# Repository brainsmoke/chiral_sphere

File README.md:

# Chiral Sphere

LED lamp based on a chiral spherical tiling consisting of 20 triangles and
12 Pentagons where the edge-length ratio triangle:pentagon is 2:1.

[Video](https://mastodon.social/@brainsmoke/111589632039788005)

# Materials

* 2x 5m WS2812 LED strips, 60 LEDs/m spacing, 10mm wide, cut into 30 strips of 17
* +/- 11 meters flexible diffuser, 12mm wide
* [custom joint PCBs [kicad]](pcb/yjoint) [[svg]](pcb/yjoint/penta_joint.svg), [untested flexpcb alternative [kicad]](pcb/yjoint_v2) [[svg]](pcb/yjoint_v2/penta_joint_v2.svg)
* [LED driver board](https://github.com/brainsmoke/leddriver3d/tree/main/pcb/driver_slim_v1), [LED driver board v2](https://github.com/brainsmoke/leddriver3d/tree/main/pcb/driver_slim_v2)
* thin wire (for connecting the data lines)
* 2x ~30cm thick wire (to handle high currents near the power connector)
* 3mm plywood, 4x 600x400mm
* white paint
* wood glue

# Maths

* [Formula for the relation between corner arc and edge-length for regular N-gons on the unit sphere](https://github.com/brainsmoke/geometry/blob/main/spherical/ngonmath.png)
* [Calculation of the corner arc for this spherical tiling](https://github.com/brainsmoke/geometry/blob/main/spherical/2tri1penta.scad#L8-L34)
* [LED Locations & normals](https://github.com/brainsmoke/geometry/blob/main/scripts/led_locations.py)

# Cutting

Based on output from [one of my scripts](https://github.com/brainsmoke/geometry/blob/main/scripts/tube.py), but
with the outer panels removed so that the tubes become U-profiles and the sides modified so that they trace
a perfect sphere.

[Laser cut shapes](cut/v1/led.svg) (with some spares; apply appropriate kerf width compensation before cutting)

# Wiring

All strips are positioned such that data-in is above data-out, with one pentagon chosen
as top.  The strips are connected as five point-symmetrical led strips with 102 LEDs each
according to [this OpenSCAD model](doc/wiring.scad).

# LED Driver

[PCB](https://github.com/brainsmoke/leddriver3d/tree/main/pcb/driver_slim_v1)

# Software

* [Driver software repo](https://github.com/brainsmoke/leddriver3d)
* [STM32 Firmware: strip5.bin](https://github.com/brainsmoke/leddriver3d/tree/main/firmware/stm32/strip5)
* [LED positions](https://github.com/brainsmoke/leddriver3d/blob/main/firmware/esp32/models/chiral_tiling/leds.json)
* [conf/hardware.json](https://github.com/brainsmoke/leddriver3d/blob/main/firmware/esp32/conf/chiral_tiling/hardware.json)

# More pictures

Add extra capacity to the strip which needs to handle the most Amps.

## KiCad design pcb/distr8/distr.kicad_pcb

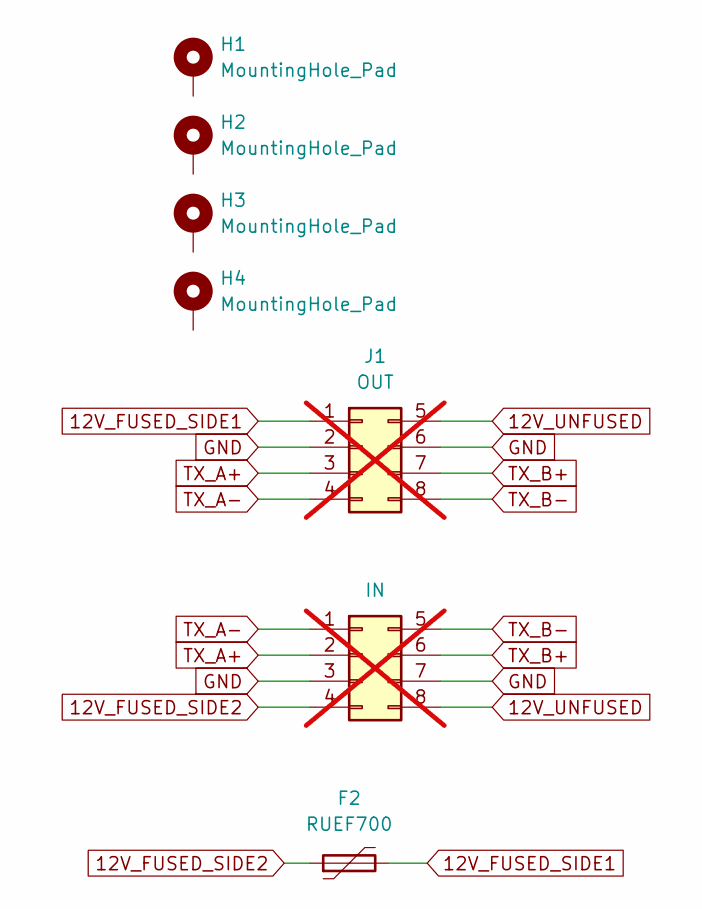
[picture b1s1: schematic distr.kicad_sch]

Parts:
F2: RUEF700; Fuse_Littlefuse_RUEF
H1, H2, H3, H4: MountingHole_Pad
J1: OUT; Molex_Micro-Fit_3.0_43045-0800_2x04_P3.00mm_Horizontal; not fitted
J2: IN; Molex_Micro-Fit_3.0_43045-0800_2x04_P3.00mm_Horizontal; not fitted

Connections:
12V_FUSED_SIDE1: F2.2, J1.1
12V_FUSED_SIDE2: F2.1, J2.4
12V_UNFUSED: J1.5, J2.8
GND: J1.2, J1.6, J2.3, J2.7
TX_A+: J1.3, J2.2
TX_A-: J1.4, J2.1
TX_B+: J1.7, J2.6
TX_B-: J1.8, J2.5

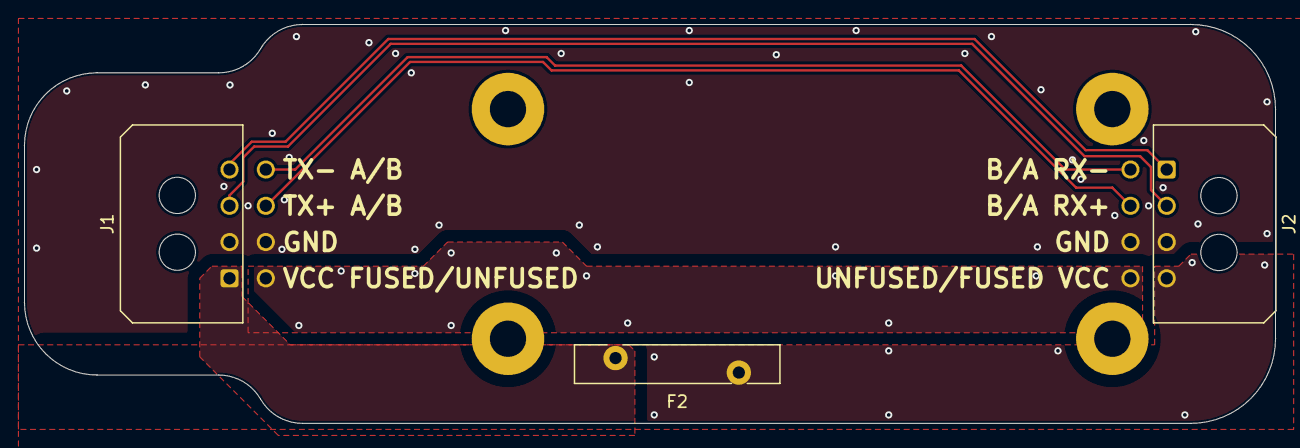
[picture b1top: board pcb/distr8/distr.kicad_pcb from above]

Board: 2 copper layers, 103.5 x 33.0 mm, 7 parts (0 on the bottom side), 8 nets.

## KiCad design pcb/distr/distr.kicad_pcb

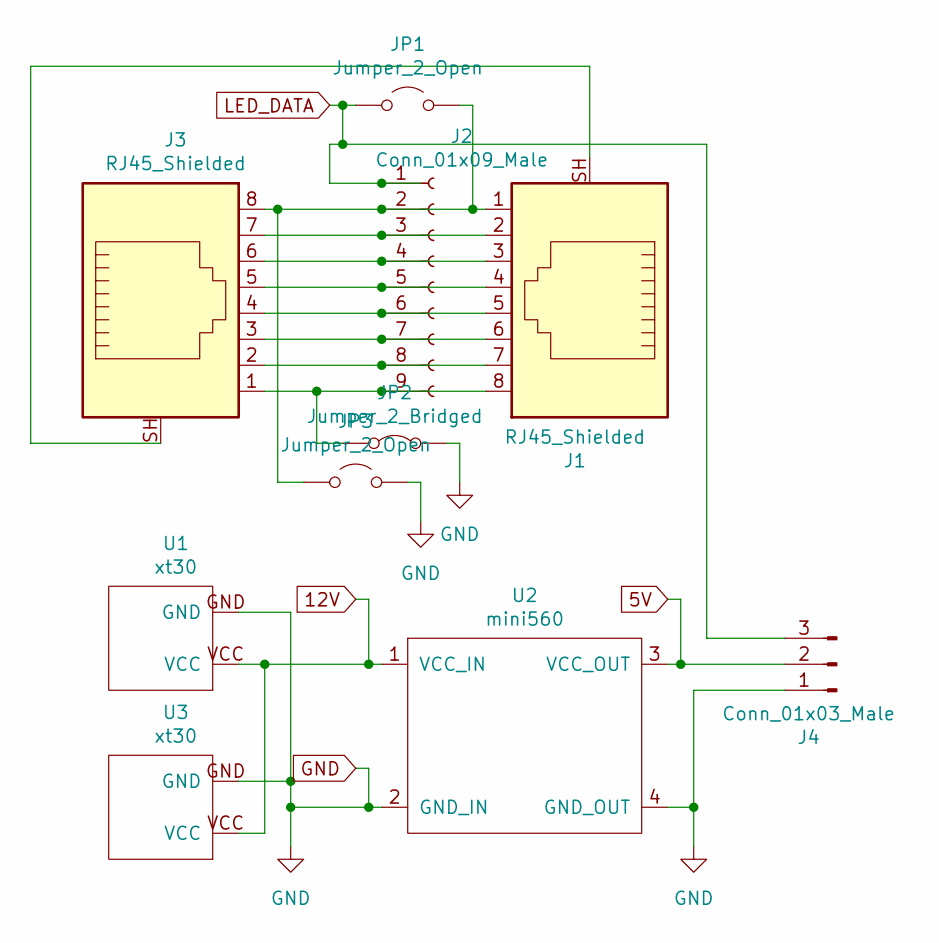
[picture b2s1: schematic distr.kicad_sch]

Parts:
J1, J3: RJ45_Shielded; HC-RJ45-055-7
J2: Conn_01x09_Male; PinHeader_1x09_P2.54mm_Vertical
J4: Conn_01x03_Male; PinHeader_1x03_P2.54mm_Vertical
JP1: Jumper_2_Open; SolderJumper-2_P1.3mm_Open_TrianglePad1.0x1.5mm
JP2: Jumper_2_Bridged; SolderJumper-2_P1.3mm_Bridged_RoundedPad1.0x1.5mm
JP3: Jumper_2_Open; SolderJumper-2_P1.3mm_Open_RoundedPad1.0x1.5mm
U1: xt30; xt30-PW-F_banana
U2: mini560
U3: xt30; xt30-PW-M_banana

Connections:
5V: J4.2, U2.3 (VCC_OUT)
12V: U1.VCC, U2.1 (VCC_IN), U3.VCC
GND: J4.1, JP2.2 (B), JP3.2 (B), U1.GND, U2.2 (GND_IN), U2.4 (GND_OUT), U3.GND
LED_DATA: J2.1, J4.3, JP1.1 (A)
unnamed: J1.SH, J3.SH
unnamed: J1.1, J2.2, J3.8, JP1.2 (B), JP3.1 (A)
unnamed: J1.2, J2.3, J3.7
unnamed: J1.3, J2.4, J3.6
unnamed: J1.4, J2.5, J3.5
unnamed: J1.5, J2.6, J3.4
unnamed: J1.6, J2.7, J3.3
unnamed: J1.7, J2.8, J3.2
unnamed: J1.8, J2.9, J3.1, JP2.1 (A)

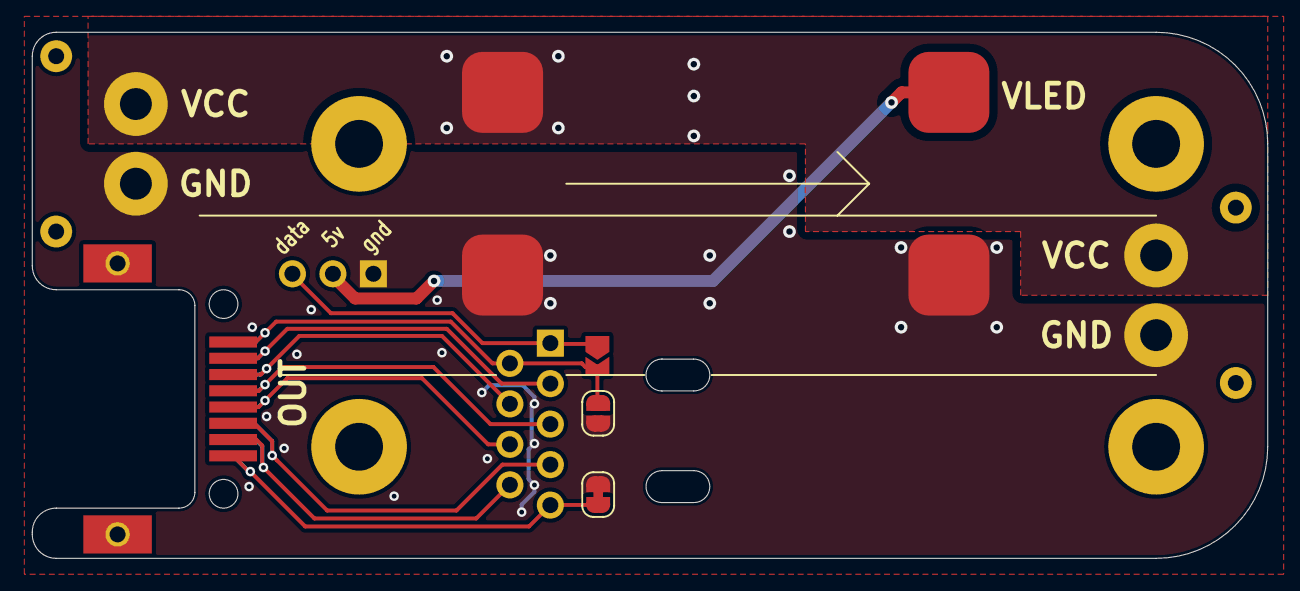
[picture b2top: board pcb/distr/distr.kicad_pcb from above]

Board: 2 copper layers, 77.5 x 33.0 mm, 10 parts (1 on the bottom side), 13 nets.

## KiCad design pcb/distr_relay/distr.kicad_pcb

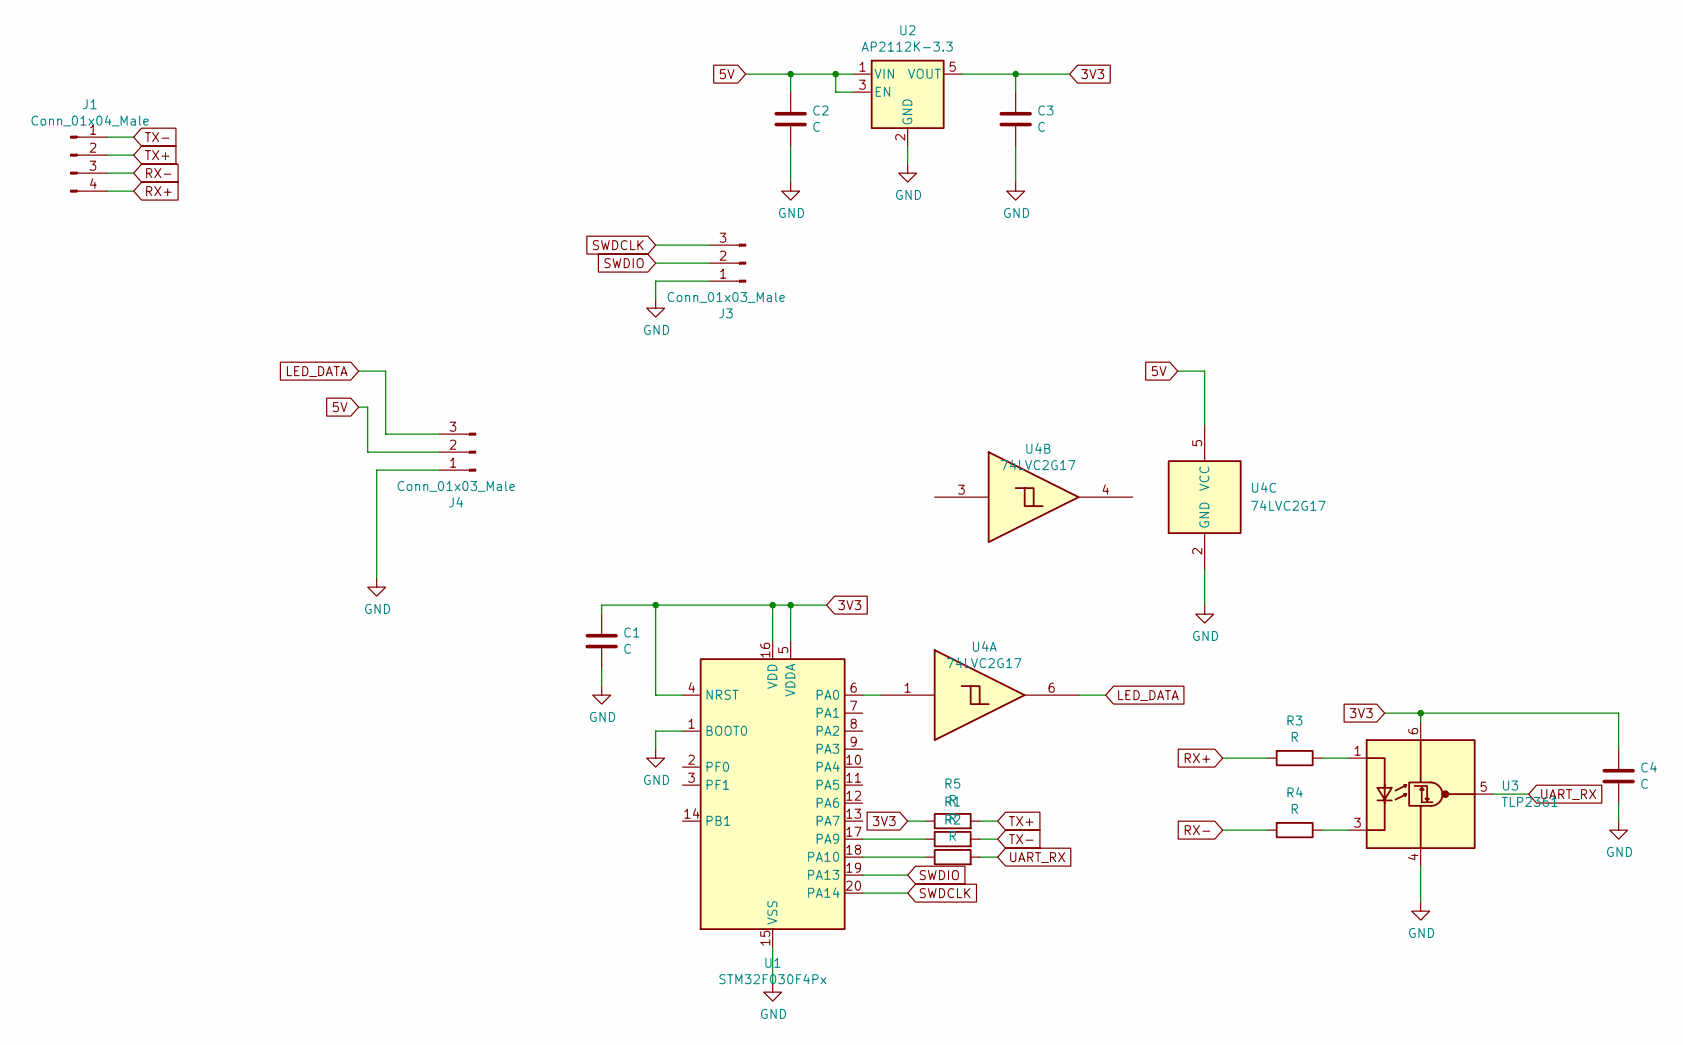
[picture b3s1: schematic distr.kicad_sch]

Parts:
C1, C2, C3, C4: C; C_0603_1608Metric
J1: Conn_01x04_Male; PinHeader_1x04_P2.54mm_Vertical
J3, J4: Conn_01x03_Male; PinHeader_1x03_P2.54mm_Vertical
R1, R2, R3, R4, R5: R; R_0603_1608Metric
U1: STM32F030F4Px; TSSOP-20_4.4x6.5mm_P0.65mm
U2: AP2112K-3.3; SOT-23-5
U3: TLP2361; SO-6_4.4x3.6mm_P1.27mm
U4: 74LVC2G17

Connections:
3V3: C1.1, C3.1, C4.1, R5.1, U1.4 (NRST), U1.5 (VDDA), U1.16 (VDD), U2.5 (VOUT), U3.6 (VDD)
5V: C2.1, J4.2, U2.1 (VIN), U2.3 (EN), U4.5 (VCC)
GND: C1.2, C2.2, C3.2, C4.2, J3.1, J4.1, U1.1 (BOOT0), U1.15 (VSS), U2.2 (GND), U3.4 (GND), U4.2 (GND)
LED_DATA: J4.3, U4.6
unnamed: U1.6 (PA0), U4.1
unnamed: R1.1, U1.17 (PA9)
unnamed: R2.1, U1.18 (PA10)
unnamed: R3.1, U3.1 (A)
unnamed: R4.1, U3.3 (K)
RX+: J1.4, R3.2
RX-: J1.3, R4.2
SWDCLK: J3.3, U1.20 (PA14)
SWDIO: J3.2, U1.19 (PA13)
TX+: J1.2, R5.2
TX-: J1.1, R1.2
UART_RX: R2.2, U3.5 (VO)

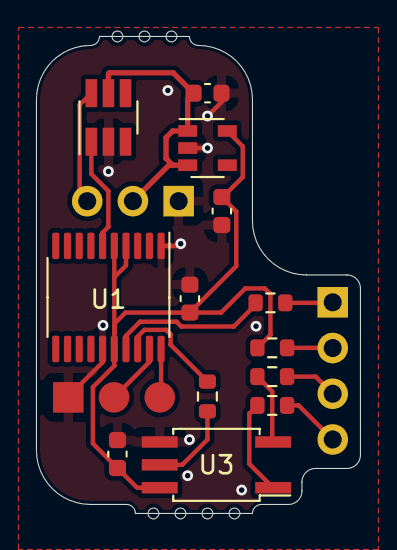
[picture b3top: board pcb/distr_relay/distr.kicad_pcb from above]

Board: 2 copper layers, 18.0 x 26.5 mm, 16 parts (0 on the bottom side), 16 nets.

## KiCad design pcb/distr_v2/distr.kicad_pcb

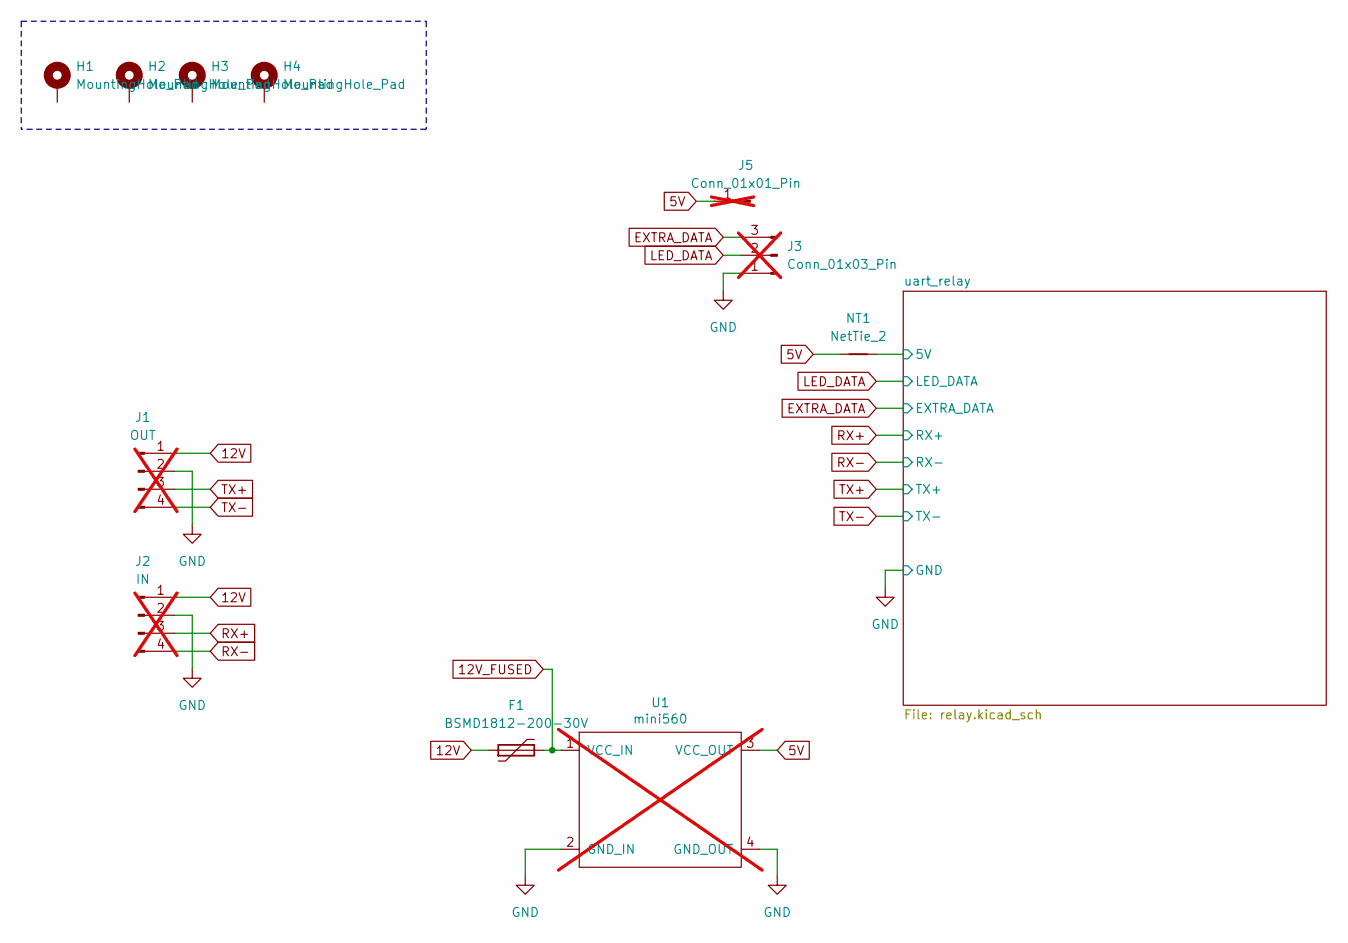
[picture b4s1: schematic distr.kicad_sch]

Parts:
F1: BSMD1812-200-30V; Fuse_1812_4532Metric; LCSC C960026
H1, H2, H3, H4: MountingHole_Pad; MountingHole_3mm_Pad_nocourtyard
J1: OUT; Molex_Micro-Fit_3.0_43650-0400_1x04_P3.00mm_Horizontal_silk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; not fitted
J2: IN; in_header; not fitted
J3: Conn_01x03_Pin; led_header_no_vcc; not fitted
J5: Conn_01x01_Pin; 5v_header; not fitted
NT1: NetTie_2; NetTie-2_SMD_Pad0.3mm
U1: mini560; mini560_minimal_silk_carveout; not fitted

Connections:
5V: J5.1, NT1.1, U1.3 (VCC_OUT)
12V: F1.1, J1.1, J2.1
12V_FUSED: F1.2, U1.1 (VCC_IN)
/uart_relay/5V: NT1.2; also elsewhere on the board
EXTRA_DATA: J3.3; also elsewhere on the board
GND: J1.2, J2.2, J3.1, U1.2 (GND_IN), U1.4 (GND_OUT); also elsewhere on the board
LED_DATA: J3.2; also elsewhere on the board
RX+: J2.3; also elsewhere on the board
RX-: J2.4; also elsewhere on the board
TX+: J1.3; also elsewhere on the board
TX-: J1.4; also elsewhere on the board

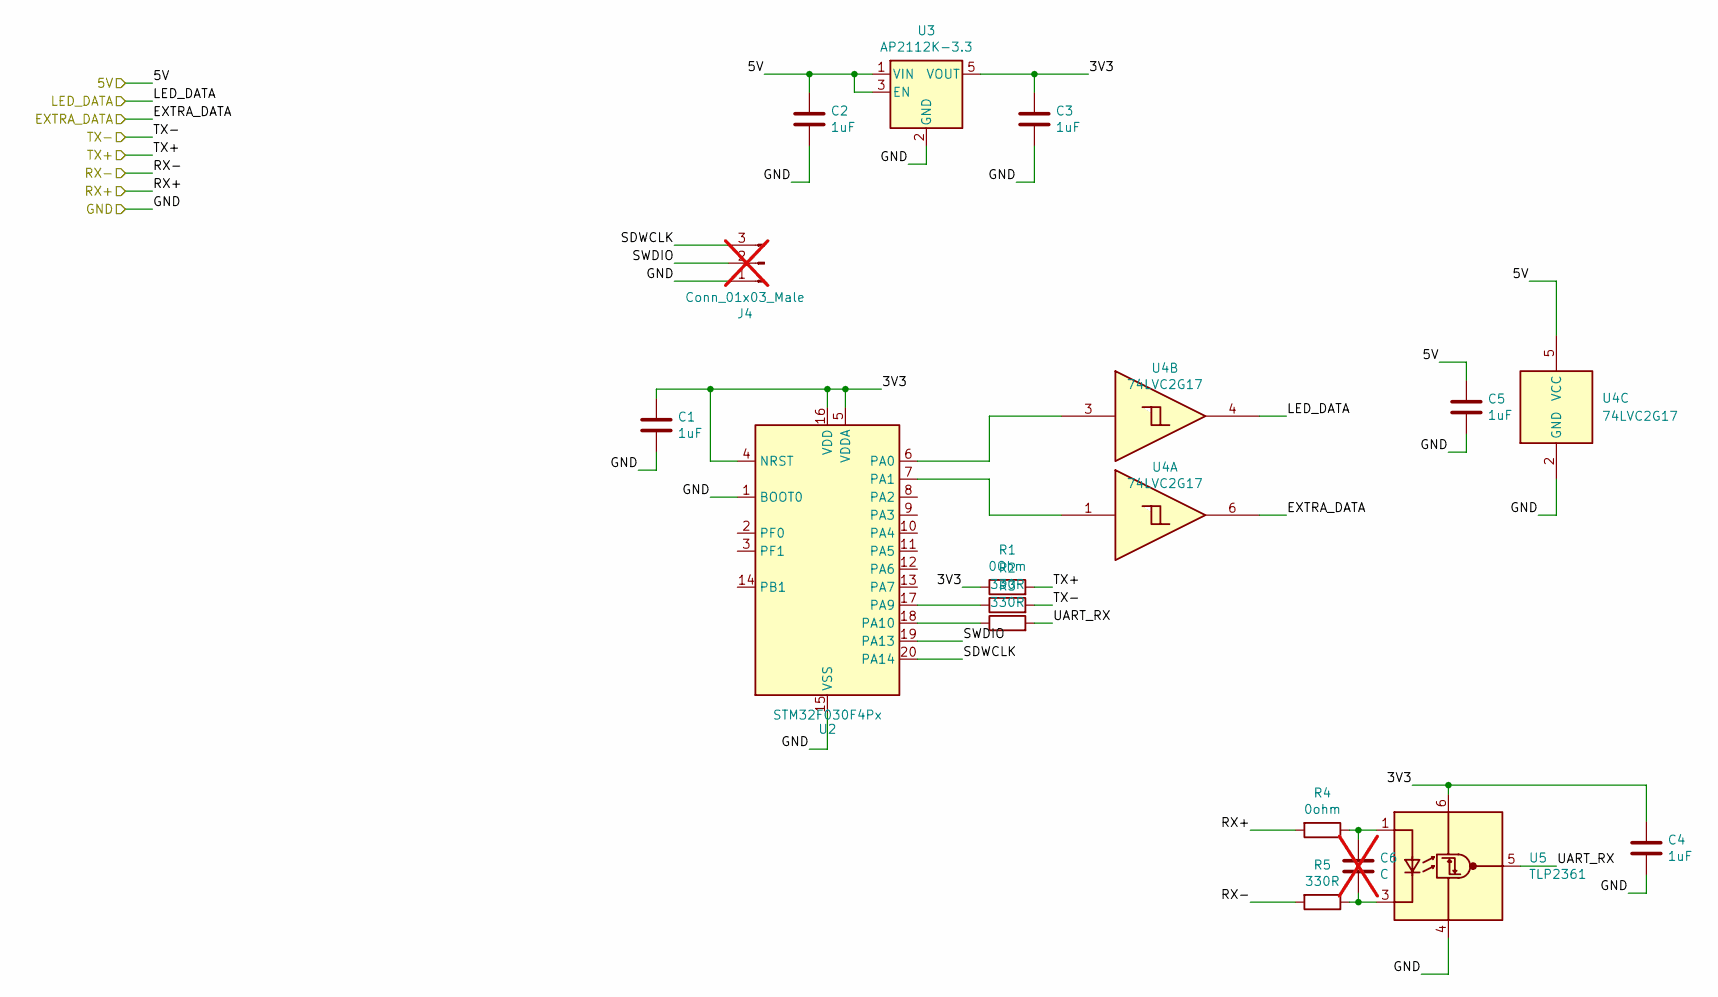
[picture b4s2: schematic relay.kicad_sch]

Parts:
C1, C2, C3, C4, C5: 1uF; C_0603_1608Metric; LCSC C15849
C6: C; C_0603_1608Metric; LCSC C15849; not fitted
J4: Conn_01x03_Male; SWD Header; not fitted
R1: 0Ohm; R_0603_1608Metric; LCSC C21189
R2, R3, R5: 330R; R_0603_1608Metric; LCSC C23138
R4: 0ohm; R_0603_1608Metric; LCSC C21189
U2: STM32F030F4Px; TSSOP-20_4.4x6.5mm_P0.65mm; LCSC C89040
U3: AP2112K-3.3; SOT-23-5; LCSC C51118
U4: 74LVC2G17; SOT-23-6_Handsoldering; LCSC C10429
U5: TLP2361; SO-5_4.4x3.6mm_P1.27mm; LCSC C107626

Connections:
/uart_relay/3V3: C1.1, C3.1, C4.1, R1.1, U2.4 (NRST), U2.5 (VDDA), U2.16 (VDD), U3.5 (VOUT), U5.6 (VDD)
/uart_relay/5V: C2.1, C5.1, U3.1 (VIN), U3.3 (EN), U4.5 (VCC); also elsewhere on the board
/uart_relay/SDWCLK: J4.3, U2.20 (PA14)
/uart_relay/SWDIO: J4.2, U2.19 (PA13)
/uart_relay/UART_RX: R3.2, U5.5 (VO)
EXTRA_DATA: U4.6; also elsewhere on the board
GND: C1.2, C2.2, C3.2, C4.2, C5.2, J4.1, U2.1 (BOOT0), U2.15 (VSS), U3.2 (GND), U4.2 (GND), U5.4 (GND); also elsewhere on the board
LED_DATA: U4.4; also elsewhere on the board
unnamed: U2.6 (PA0), U4.3
unnamed: U2.7 (PA1), U4.1
unnamed: R2.1, U2.17 (PA9)
unnamed: R3.1, U2.18 (PA10)
unnamed: C6.1, R4.1, U5.1 (A)
unnamed: C6.2, R5.1, U5.3 (K)
RX+: R4.2; also elsewhere on the board
RX-: R5.2; also elsewhere on the board
TX+: R1.2; also elsewhere on the board
TX-: R2.2; also elsewhere on the board

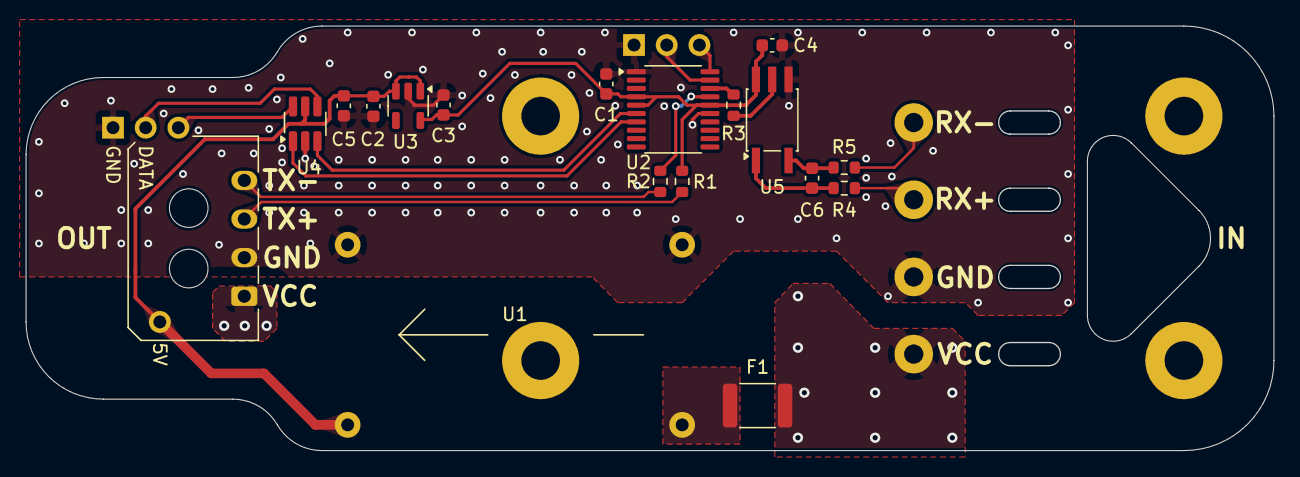
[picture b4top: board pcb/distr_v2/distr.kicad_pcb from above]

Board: 2 copper layers, 97.0 x 33.0 mm, 27 parts (1 on the bottom side), 21 nets.

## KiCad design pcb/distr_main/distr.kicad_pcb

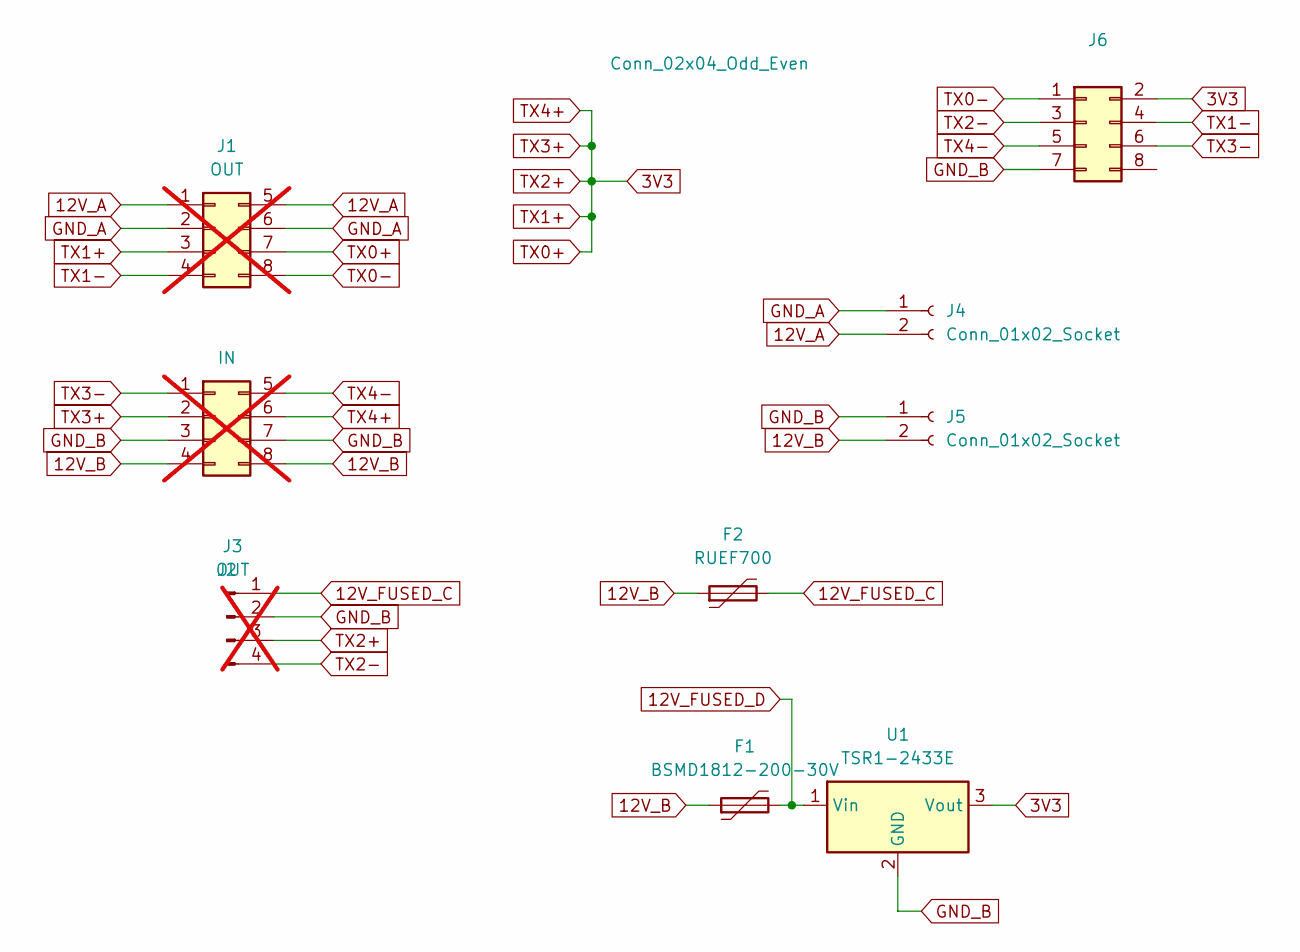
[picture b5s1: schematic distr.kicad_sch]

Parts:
F1: BSMD1812-200-30V; Fuse_1812_4532Metric; LCSC C960026
F2: RUEF700; Fuse_Littlefuse_RUEF
J1: OUT; Molex_Micro-Fit_3.0_43045-0800_2x04_P3.00mm_Horizontal; not fitted
J2: IN; Molex_Micro-Fit_3.0_43045-0800_2x04_P3.00mm_Horizontal; not fitted
J3: OUT; Molex_Micro-Fit_3.0_43650-0400_1x04_P3.00mm_Horizontal_silk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; not fitted
J4, J5: Conn_01x02_Socket; AMASS_XT60-F_1x02_P7.20mm_Vertical
J6: Conn_02x04_Odd_Even; PinSocket_2x04_P2.54mm_Vertical
U1: TSR1-2433E; Converter_DCDC_TRACO_TSR1-xxxxE_THT

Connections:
3V3: J1.3, J1.7, J2.2, J2.6, J3.3, J6.2, U1.3 (Vout)
12V_A: J1.1, J1.5, J4.2
12V_B: F1.1, F2.1, J2.4, J2.8, J5.2
12V_FUSED_C: F2.2, J3.1
12V_FUSED_D: F1.2, U1.1 (Vin)
GND_A: J1.2, J1.6, J4.1
GND_B: J2.3, J2.7, J3.2, J5.1, J6.7, U1.2 (GND)
TX0-: J1.8, J6.1
TX1-: J1.4, J6.4
TX2-: J3.4, J6.3
TX3-: J2.1, J6.6
TX4-: J2.5, J6.5

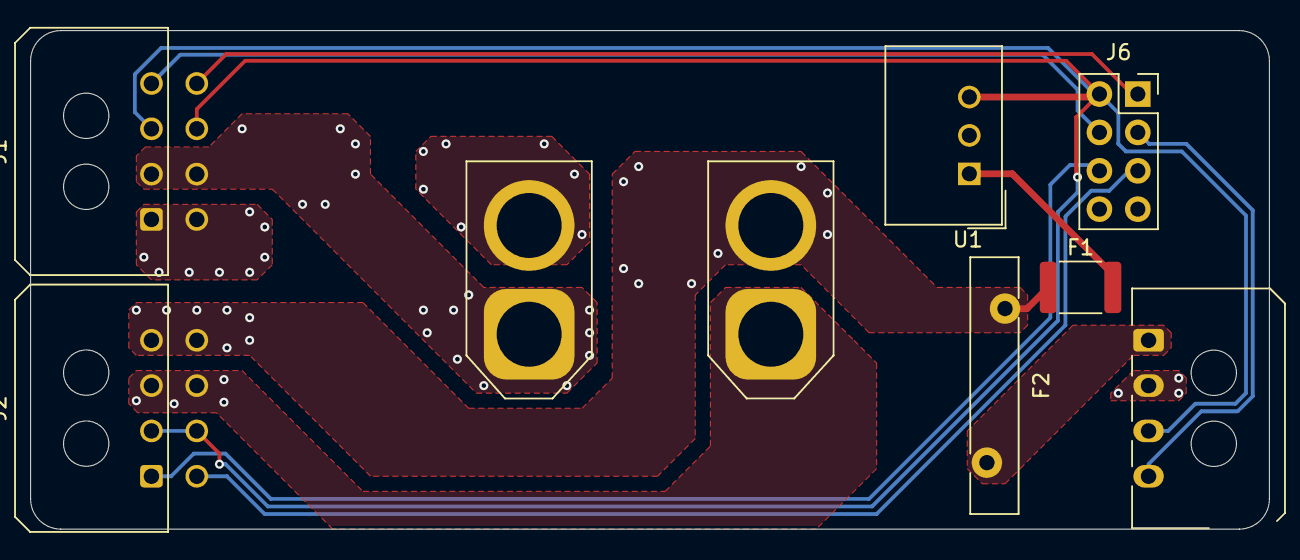
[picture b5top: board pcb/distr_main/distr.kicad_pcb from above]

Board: 4 copper layers, 82.0 x 33.0 mm, 9 parts (0 on the bottom side), 12 nets.

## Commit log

2023-12-16 move data into separate repo
2023-12-16 add images
2023-12-16 edit readme
2023-12-16 add photos
2023-12-16 move text
2023-12-16 grammar
2023-12-17 typo
2023-12-17 add info about driver board
2023-12-17 add software stuff
2023-12-17 clarification
2023-12-17 readme
2023-12-17 remove json comma
2023-12-17 Laser cut desciption
2023-12-17 add driver picture
2023-12-17 add link to video
2023-12-17 add led location calculations
2023-12-17 formatting error
2023-12-17 add led strip spacing detail
2023-12-18 minor tweak
2023-12-29 update docs
2024-01-13 README: update links
2024-01-31 move pcb files
2024-01-31 add (untested) flexpcb
2024-02-01 reduce number of holes
2024-02-01 minor readme edit
2024-03-05 add strip numbering & top side annotation
2024-03-05 add reference to driver board v2
2024-04-18 power dist pcb for bigger sphere
2024-04-20 move laser cut files
2024-04-20 add cutting files for a bigger sphere
2024-04-21 fix filename to match number of copies required
2024-04-21 add missing panel
2024-04-23 remove unused paths, add generator command for reference
2024-04-26 add alternative tops
2024-04-27 alternative top facets
2024-05-12 add final piece
2024-05-12 commit new cutting sheets
2024-05-12 rename alternative cutting sheet -> default
2024-05-31 add opto distribution board
2024-06-11 update link
2024-12-04 new hanger
2025-01-01 add big sphere assembly documentation
2025-01-01 fix arrows
2025-01-02 add assambly toold
2025-01-03 add instructions
2025-01-03 add assembly tool
2025-01-07 kicad 8
2025-04-24 add tool to align connectors for the big sphere
2025-08-30 v2 segment pcb
2025-08-30 modified hanger for the small ball
2025-09-14 add PCBs with fuses, port to kicad 9
2025-09-14 git ignore pcb backups
2025-09-14 add gerbers
2025-09-14 add missing rules.mk
2025-09-14 add cut files for a small tetrahedral sphere
2025-09-14 add unfinished design for case padding
2025-09-14 make PCBA file generation optional
2025-09-14 ignore tmp builddir
2025-09-14 fix links
2025-09-18 re-label segments in assembly manual
2025-09-26 add wire guide model
2025-09-26 laser cut drawing for bottom plate with xt60 cutout
2025-09-26 update assembly manual
2025-10-01 add power connector stiffner cad files
2025-10-01 add manual/instructions
2025-10-01 add combined manual
2025-10-01 remove pngs
2025-10-01 add missing connector in schematic
2025-10-01 add missing connector to manual
2025-10-01 fix number of S segments
2025-10-01 fix cosmetic imperfection
2025-10-01 rename ring segments in documentation
2025-10-01 use more logical ordering of segments
2025-10-02 remove intermediate pdfs
2025-10-02 add png target
2025-10-04 add [dis]assembly tools for new design
2026-01-09 fix links to renames repo
2026-01-13 add wire(-connection) clamp model
